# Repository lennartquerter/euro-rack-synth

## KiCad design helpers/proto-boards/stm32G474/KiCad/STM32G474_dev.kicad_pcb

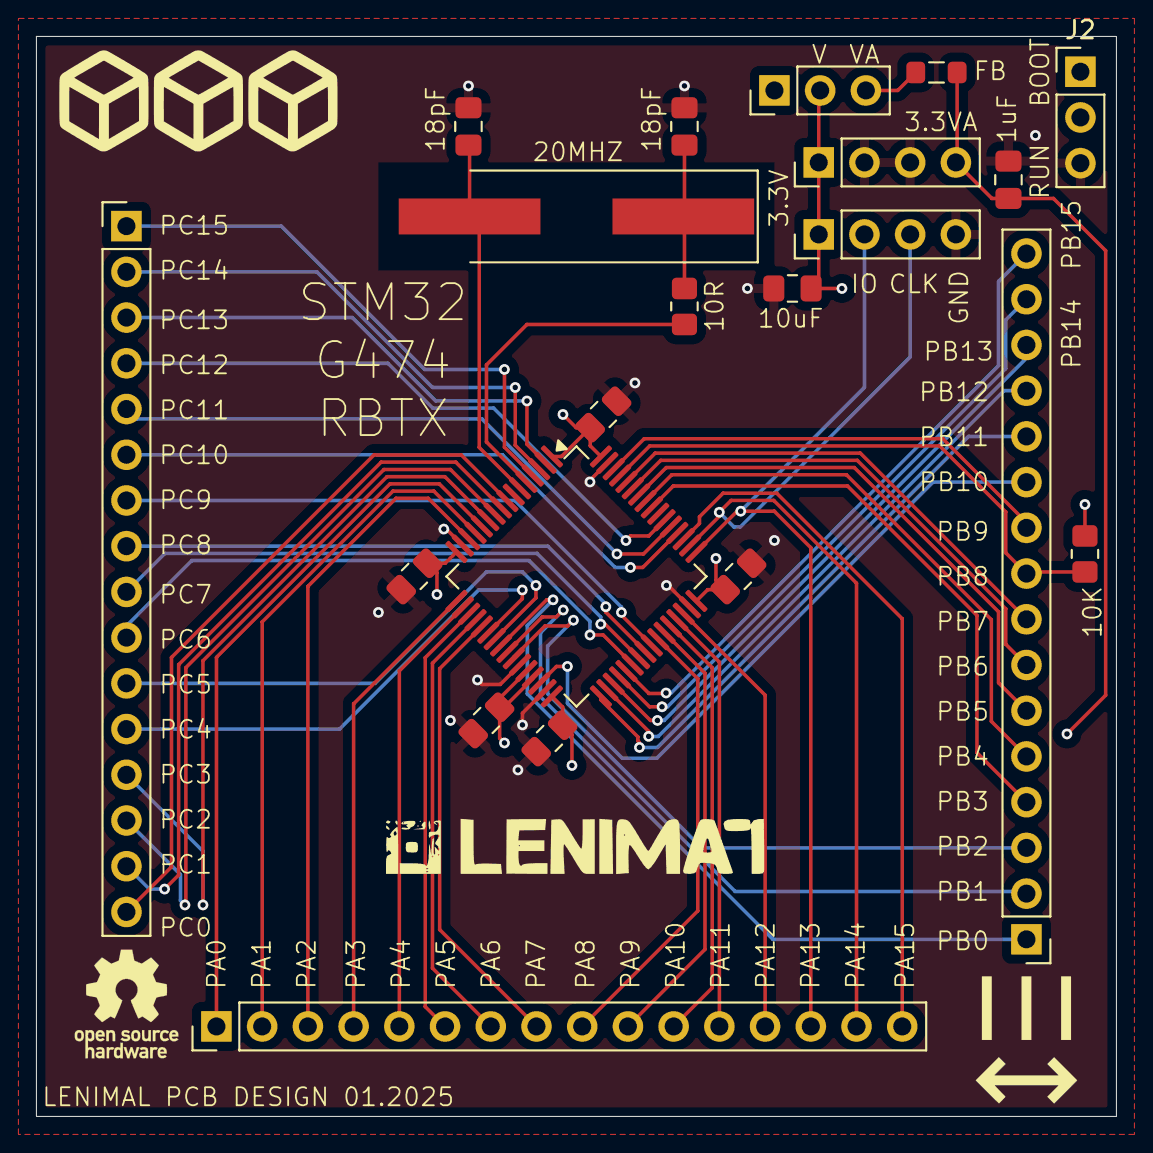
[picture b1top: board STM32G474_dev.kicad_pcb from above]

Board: 4 copper layers, 60.0 x 60.0 mm, 21 parts (0 on the bottom side), 56 nets.

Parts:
C1, C2, C3, C4, C6: 100nF; C_0805_2012Metric_Pad1.18x1.45mm_HandSolder
C5: 10uF; C_0805_2012Metric_Pad1.18x1.45mm_HandSolder
C7: 1uF; C_0805_2012Metric_Pad1.18x1.45mm_HandSolder
C9, C11: 10pF; C_0805_2012Metric_Pad1.18x1.45mm_HandSolder
FB: 120R; L_0805_2012Metric_Pad1.05x1.20mm_HandSolder
J1: SWD; PinHeader_1x04_P2.54mm_Vertical
J2: BOOT_RUN; PinHeader_1x03_P2.54mm_Vertical
J3, J4, J5: Conn_01x16; PinHeader_1x16_P2.54mm_Vertical
J6: POWER_HEADER; PinHeader_1x04_P2.54mm_Vertical
J7: V_VA_CONN; PinHeader_1x03_P2.54mm_Vertical
R2: 10R; R_0805_2012Metric_Pad1.20x1.40mm_HandSolder
R3: 10K; R_0805_2012Metric_Pad1.20x1.40mm_HandSolder
U1: STM32G474RBTx; LQFP-64_10x10mm_P0.5mm
Y1: 20MHZ; Crystal_SMD_HC49-SD_HandSoldering

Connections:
+3.3V: C1.2, C2.2, C3.2, C4.2, C5.2, J1.1, J2.1, J6.1, J7.2, U1.1 (VBAT), U1.16 (VDD), U1.32 (VDD), U1.48 (VDD), U1.64 (VDD)
+3.3VA: C6.2, C7.2, FB.1, J6.4, U1.28 (VREF+), U1.29 (VDDA)
/BOOT0: J5.9, R3.2, U1.61 (PB8)
/HSC_IN: R2.2, U1.5 (PF0)
/HSC_OUT: C11.1, U1.6 (PF1), Y1.2
/SWD_CLK: J1.3, J4.15, U1.50 (PA14)
/SWD_IO: J1.2, J4.14, U1.49 (PA13)
GNDREF: C1.1, C2.1, C3.1, C4.1, C5.1, C6.1, C7.1, C9.2, C11.2, J1.4, J2.3, J6.2, J6.3, U1.15 (VSS), U1.27 (VSSA), U1.31 (VSS), U1.47 (VSS), U1.63 (VSS)
unnamed: C9.1, R2.1, Y1.1
unnamed: J2.2, R3.1
unnamed: J3.1, U1.4 (PC15)
unnamed: J3.2, U1.3 (PC14)
unnamed: J3.3, U1.2 (PC13)
unnamed: J3.4, U1.54 (PC12)
unnamed: J3.5, U1.53 (PC11)
unnamed: J3.6, U1.52 (PC10)
unnamed: J3.7, U1.41 (PC9)
unnamed: J3.8, U1.40 (PC8)
unnamed: J3.9, U1.39 (PC7)
unnamed: J3.10, U1.38 (PC6)
unnamed: J3.11, U1.23 (PC5)
unnamed: J3.12, U1.22 (PC4)
unnamed: J3.13, U1.11 (PC3)
unnamed: J3.14, U1.10 (PC2)
unnamed: J3.15, U1.9 (PC1)
unnamed: J3.16, U1.8 (PC0)
unnamed: J4.1, U1.12 (PA0)
unnamed: J4.2, U1.13 (PA1)
unnamed: J4.3, U1.14 (PA2)
unnamed: J4.4, U1.17 (PA3)
unnamed: J4.5, U1.18 (PA4)
unnamed: J4.6, U1.19 (PA5)
unnamed: J4.7, U1.20 (PA6)
unnamed: J4.8, U1.21 (PA7)
unnamed: J4.9, U1.42 (PA8)
unnamed: J4.10, U1.43 (PA9)
unnamed: J4.11, U1.44 (PA10)
unnamed: J4.12, U1.45 (PA11)
unnamed: J4.13, U1.46 (PA12)
unnamed: J4.16, U1.51 (PA15)
unnamed: J5.1, U1.24 (PB0)
unnamed: J5.2, U1.25 (PB1)
unnamed: J5.3, U1.26 (PB2)
unnamed: J5.4, U1.56 (PB3)
unnamed: J5.5, U1.57 (PB4)
unnamed: J5.6, U1.58 (PB5)
unnamed: J5.7, U1.59 (PB6)
unnamed: J5.8, U1.60 (PB7)
unnamed: J5.10, U1.62 (PB9)
unnamed: J5.11, U1.30 (PB10)
unnamed: J5.12, U1.33 (PB11)
unnamed: J5.13, U1.34 (PB12)
unnamed: J5.14, U1.35 (PB13)
unnamed: J5.15, U1.36 (PB14)
unnamed: J5.16, U1.37 (PB15)
unnamed: FB.2, J7.3

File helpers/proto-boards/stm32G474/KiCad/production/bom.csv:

Designator,Footprint,Quantity,Value,LCSC Part #
"C1, C2, C3, C4, C6",0805,5,100nF,
"C11, C9",0805,2,10pF,
C5,0805,1,10uF,
C7,0805,1,1uF,
FB,0805,1,120R,
J1,PinHeader_1x04_P2.54mm_Vertical,1,SWD,
J2,PinHeader_1x03_P2.54mm_Vertical,1,BOOT_RUN,
"J3, J4, J5",PinHeader_1x16_P2.54mm_Vertical,3,Conn_01x16,
J6,PinHeader_1x04_P2.54mm_Vertical,1,POWER_HEADER,
J7,PinHeader_1x03_P2.54mm_Vertical,1,V_VA_CONN,
R2,0805,1,10R,
R3,0805,1,10K,
U1,LQFP-64_10x10mm_P0.5mm,1,STM32G474RBTx,
Y1,Crystal_SMD_HC49-SD_HandSoldering,1,20MHZ,

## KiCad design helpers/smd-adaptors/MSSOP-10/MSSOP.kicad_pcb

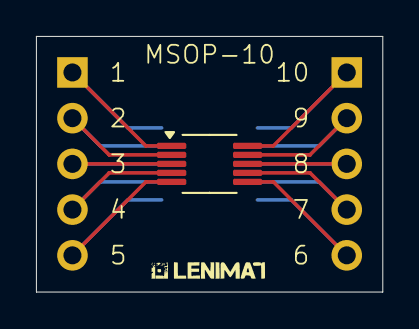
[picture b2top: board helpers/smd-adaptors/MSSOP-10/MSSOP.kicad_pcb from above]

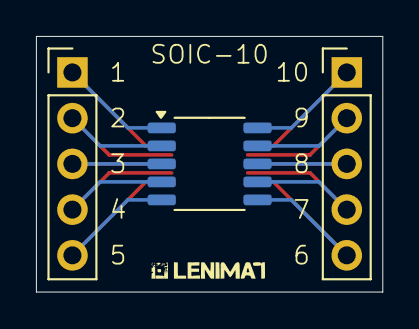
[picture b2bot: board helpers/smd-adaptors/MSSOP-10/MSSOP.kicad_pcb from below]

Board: 2 copper layers, 19.2 x 14.2 mm, 4 parts (3 on the bottom side), 10 nets.

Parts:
J1, J2: Conn_01x05; PinHeader_1x05_P2.54mm_Vertical
J3: Conn_01x10; MSOP-10_3x3mm_P0.5mm
J4: Conn_01x10; SOIC-10_3.9x4.9mm_P1mm

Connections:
unnamed: J1.1, J3.10, J4.1
unnamed: J1.2, J3.9, J4.2
unnamed: J1.3, J3.8, J4.3
unnamed: J1.4, J3.7, J4.4
unnamed: J1.5, J3.6, J4.5
unnamed: J2.1, J3.1, J4.10
unnamed: J2.2, J3.2, J4.9
unnamed: J2.3, J3.3, J4.8
unnamed: J2.4, J3.4, J4.7
unnamed: J2.5, J3.5, J4.6

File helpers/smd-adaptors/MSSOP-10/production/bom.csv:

Designator,Footprint,Quantity,Value,LCSC Part #
"J1, J2",PinHeader_1x05_P2.54mm_Vertical,2,Conn_01x05,
J3,MSOP-10_3x3mm_P0.5mm,1,Conn_01x10,
J4,SOIC-10_3.9x4.9mm_P1mm,1,Conn_01x10,

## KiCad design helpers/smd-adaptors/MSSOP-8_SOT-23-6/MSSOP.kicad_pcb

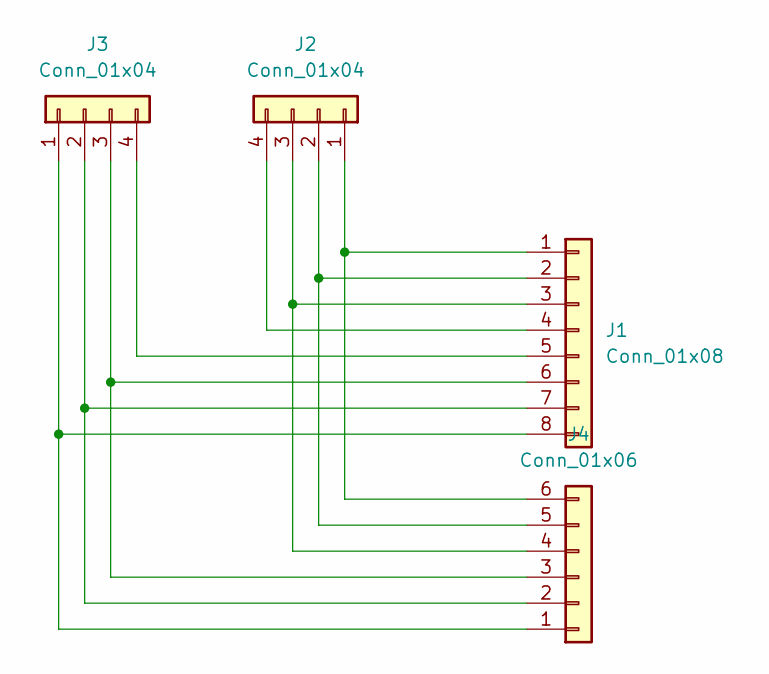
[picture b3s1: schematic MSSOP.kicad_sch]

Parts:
J1: Conn_01x08; MSOP-8_3x3mm_P0.65mm
J2, J3: Conn_01x04; PinHeader_1x04_P2.54mm_Vertical
J4: Conn_01x06; SOT-23-6_Handsoldering

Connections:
unnamed: J1.1, J2.1, J4.6
unnamed: J1.2, J2.2, J4.5
unnamed: J1.3, J2.3, J4.4
unnamed: J1.4, J2.4
unnamed: J1.5, J3.4
unnamed: J1.6, J3.3, J4.3
unnamed: J1.7, J3.2, J4.2
unnamed: J1.8, J3.1, J4.1

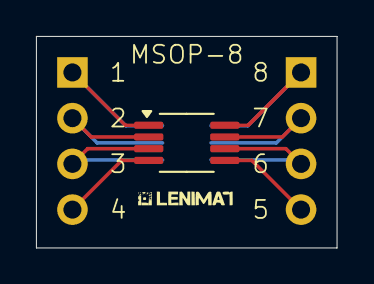
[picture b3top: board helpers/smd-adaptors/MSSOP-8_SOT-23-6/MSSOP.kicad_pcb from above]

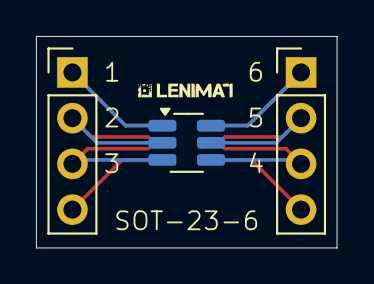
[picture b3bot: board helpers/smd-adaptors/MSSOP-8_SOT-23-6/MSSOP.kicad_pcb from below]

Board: 2 copper layers, 16.7 x 11.8 mm, 4 parts (3 on the bottom side), 8 nets.

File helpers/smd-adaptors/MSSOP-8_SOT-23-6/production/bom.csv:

Designator,Footprint,Quantity,Value,LCSC Part #
J1,MSOP-8_3x3mm_P0.65mm,1,Conn_01x08,
"J2, J3",PinHeader_1x04_P2.54mm_Vertical,2,Conn_01x04,
J4,SOT-23-6_Handsoldering,1,Conn_01x06,

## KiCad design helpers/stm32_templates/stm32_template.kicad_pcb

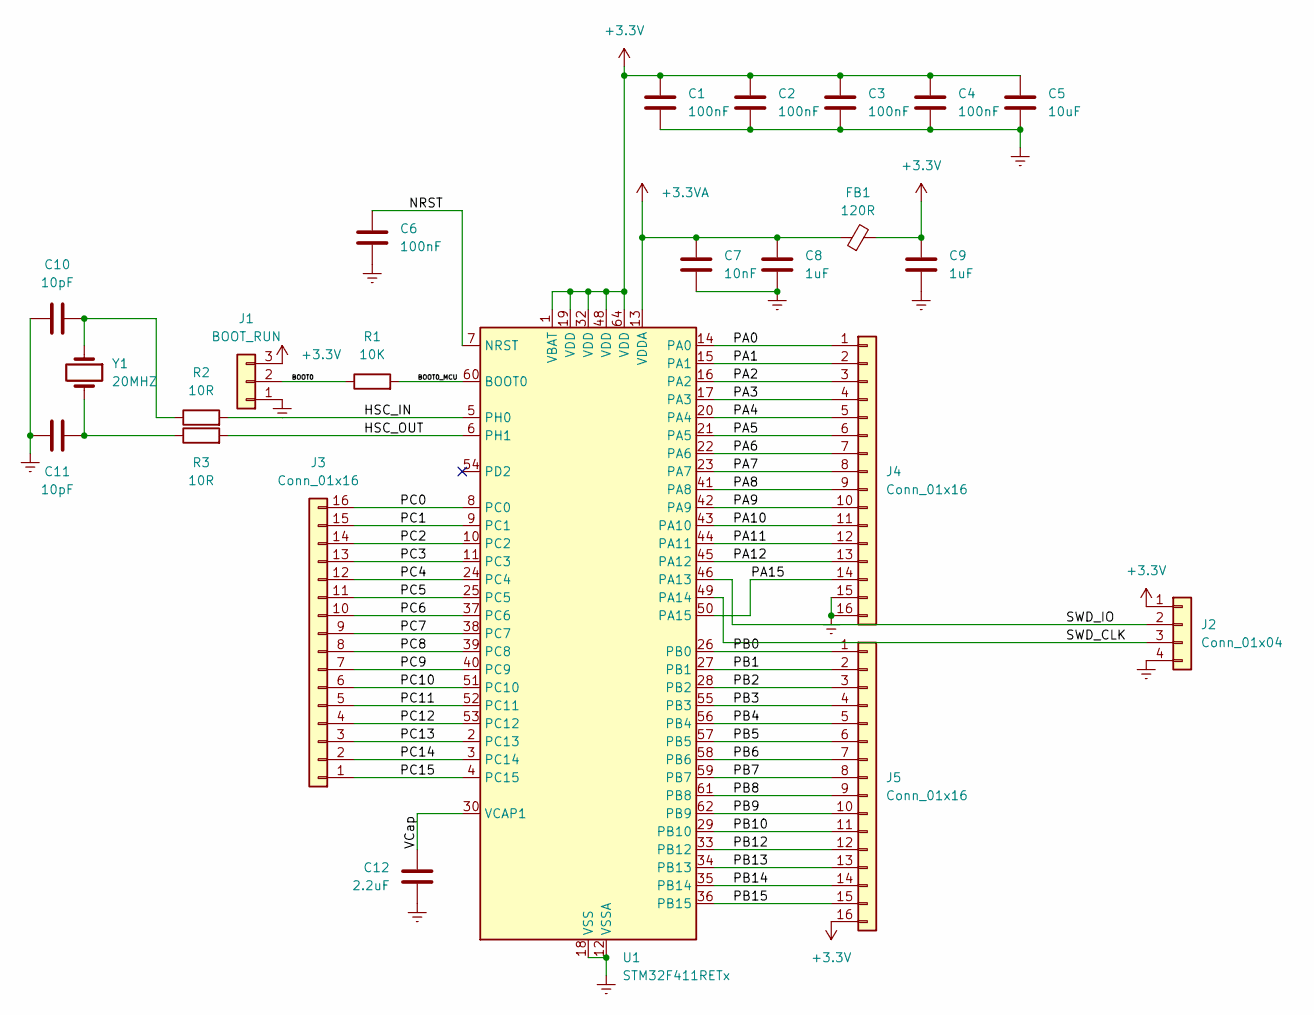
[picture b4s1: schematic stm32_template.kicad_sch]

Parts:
C1, C2, C3, C4, C6: 100nF; C_0805_2012Metric_Pad1.18x1.45mm_HandSolder
C5: 10uF; C_0805_2012Metric_Pad1.18x1.45mm_HandSolder
C7: 10nF; C_0805_2012Metric_Pad1.18x1.45mm_HandSolder
C8, C9: 1uF; C_0805_2012Metric_Pad1.18x1.45mm_HandSolder
C10, C11: 10pF; C_0805_2012Metric_Pad1.18x1.45mm_HandSolder
C12: 2.2uF; C_0805_2012Metric_Pad1.18x1.45mm_HandSolder
FB1: 120R; L_0805_2012Metric_Pad1.05x1.20mm_HandSolder
J1: BOOT_RUN; PinHeader_1x03_P2.54mm_Vertical
J2: Conn_01x04; PinHeader_1x04_P2.54mm_Vertical
J3, J4, J5: Conn_01x16; PinHeader_1x16_P2.54mm_Vertical
R1: 10K; R_0805_2012Metric_Pad1.20x1.40mm_HandSolder
R2, R3: 10R; R_0805_2012Metric_Pad1.20x1.40mm_HandSolder
U1: STM32F411RETx; LQFP-64_10x10mm_P0.5mm
Y1: 20MHZ; Crystal_SMD_HC49-SD_HandSoldering

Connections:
+3.3V: C1.2, C2.2, C3.2, C4.2, C5.2, C9.2, FB1.2, J1.3, J2.1, J5.16, U1.1 (VBAT), U1.19 (VDD), U1.32 (VDD), U1.48 (VDD), U1.64 (VDD)
+3.3VA: C7.2, C8.2, FB1.1, U1.13 (VDDA)
/BOOT0: J1.2, R1.1
/BOOT0_MCU: R1.2, U1.60 (BOOT0)
/HSC_IN: R2.2, U1.5 (PH0)
/HSC_OUT: R3.2, U1.6 (PH1)
/NRST: C6.1, U1.7 (NRST)
/PA0: J4.1, U1.14 (PA0)
/PA1: J4.2, U1.15 (PA1)
/PA2: J4.3, U1.16 (PA2)
/PA3: J4.4, U1.17 (PA3)
/PA4: J4.5, U1.20 (PA4)
/PA5: J4.6, U1.21 (PA5)
/PA6: J4.7, U1.22 (PA6)
/PA7: J4.8, U1.23 (PA7)
/PA8: J4.9, U1.41 (PA8)
/PA9: J4.10, U1.42 (PA9)
/PA10: J4.11, U1.43 (PA10)
/PA11: J4.12, U1.44 (PA11)
/PA12: J4.13, U1.45 (PA12)
/PA15: J4.14, U1.50 (PA15)
/PB0: J5.1, U1.26 (PB0)
/PB1: J5.2, U1.27 (PB1)
/PB2: J5.3, U1.28 (PB2)
/PB3: J5.4, U1.55 (PB3)
/PB4: J5.5, U1.56 (PB4)
/PB5: J5.6, U1.57 (PB5)
/PB6: J5.7, U1.58 (PB6)
/PB7: J5.8, U1.59 (PB7)
/PB8: J5.9, U1.61 (PB8)
/PB9: J5.10, U1.62 (PB9)
/PB10: J5.11, U1.29 (PB10)
/PB12: J5.12, U1.33 (PB12)
/PB13: J5.13, U1.34 (PB13)
/PB14: J5.14, U1.35 (PB14)
/PB15: J5.15, U1.36 (PB15)
/PC0: J3.16, U1.8 (PC0)
/PC1: J3.15, U1.9 (PC1)
/PC2: J3.14, U1.10 (PC2)
/PC3: J3.13, U1.11 (PC3)
/PC4: J3.12, U1.24 (PC4)
/PC5: J3.11, U1.25 (PC5)
/PC6: J3.10, U1.37 (PC6)
/PC7: J3.9, U1.38 (PC7)
/PC8: J3.8, U1.39 (PC8)
/PC9: J3.7, U1.40 (PC9)
/PC10: J3.6, U1.51 (PC10)
/PC11: J3.5, U1.52 (PC11)
/PC12: J3.4, U1.53 (PC12)
/PC13: J3.3, U1.2 (PC13)
/PC14: J3.2, U1.3 (PC14)
/PC15: J3.1, U1.4 (PC15)
/SWD_CLK: J2.3, U1.49 (PA14)
/SWD_IO: J2.2, U1.46 (PA13)
/VCap: C12.1, U1.30 (VCAP1)
GNDREF: C1.1, C2.1, C3.1, C4.1, C5.1, C6.2, C7.1, C8.1, C9.1, C10.2, C11.2, C12.2, J1.1, J2.4, J4.15, J4.16, U1.12 (VSSA), U1.18 (VSS), U1.31 (VSS), U1.47 (VSS), U1.63 (VSS)
unnamed: C10.1, R2.1, Y1.1
unnamed: C11.1, R3.1, Y1.2

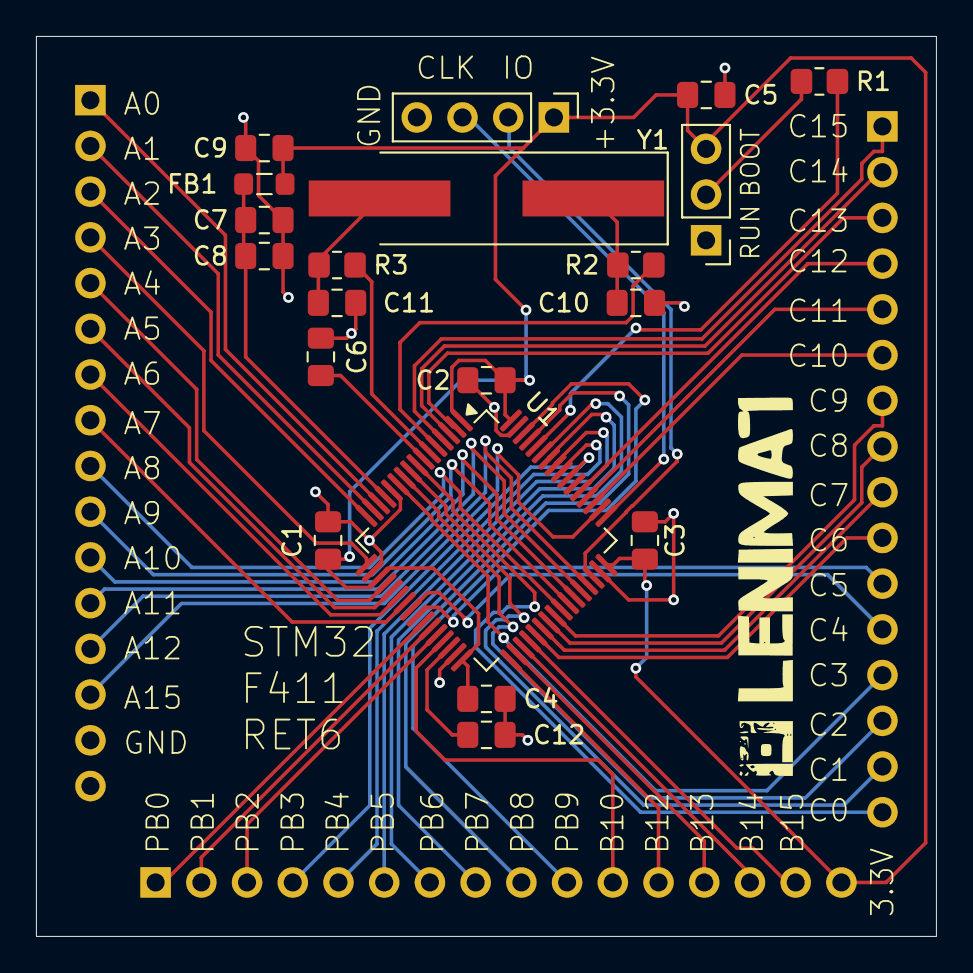
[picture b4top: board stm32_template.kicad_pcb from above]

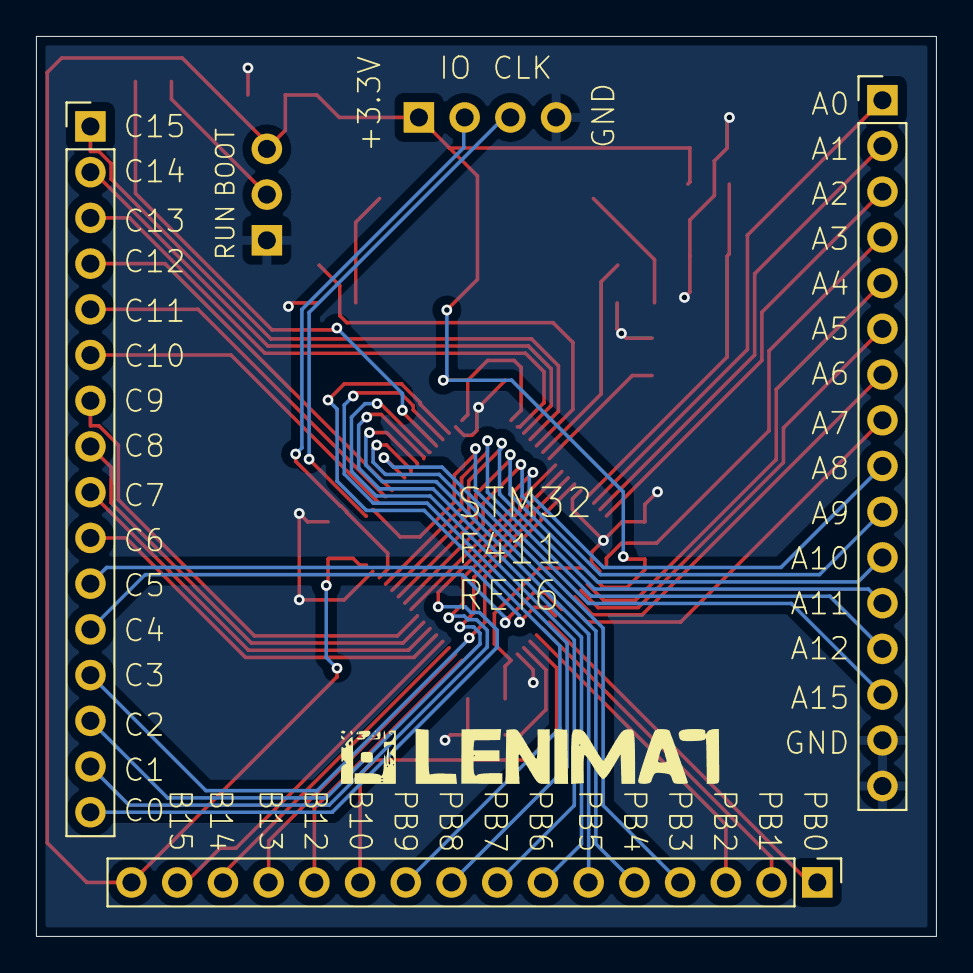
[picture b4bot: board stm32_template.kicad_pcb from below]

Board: 2 copper layers, 50.0 x 50.0 mm, 23 parts (3 on the bottom side), 58 nets.

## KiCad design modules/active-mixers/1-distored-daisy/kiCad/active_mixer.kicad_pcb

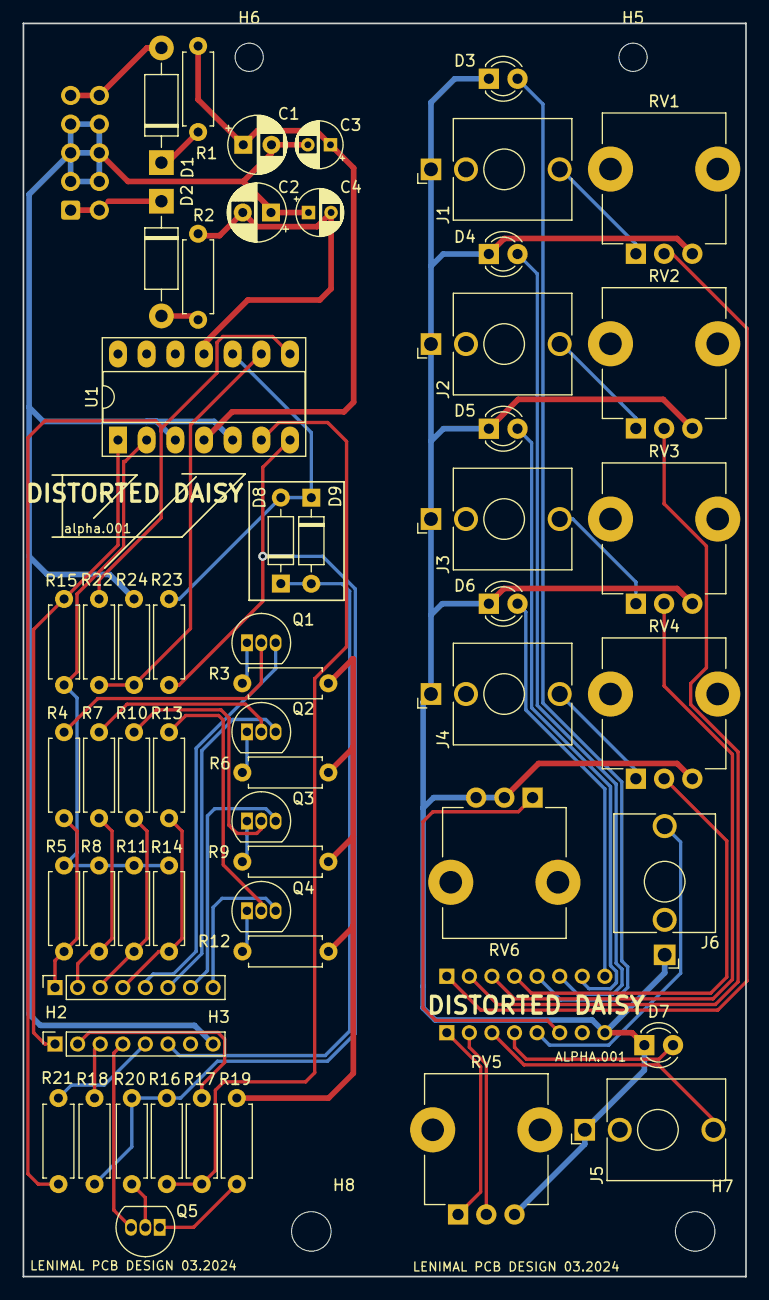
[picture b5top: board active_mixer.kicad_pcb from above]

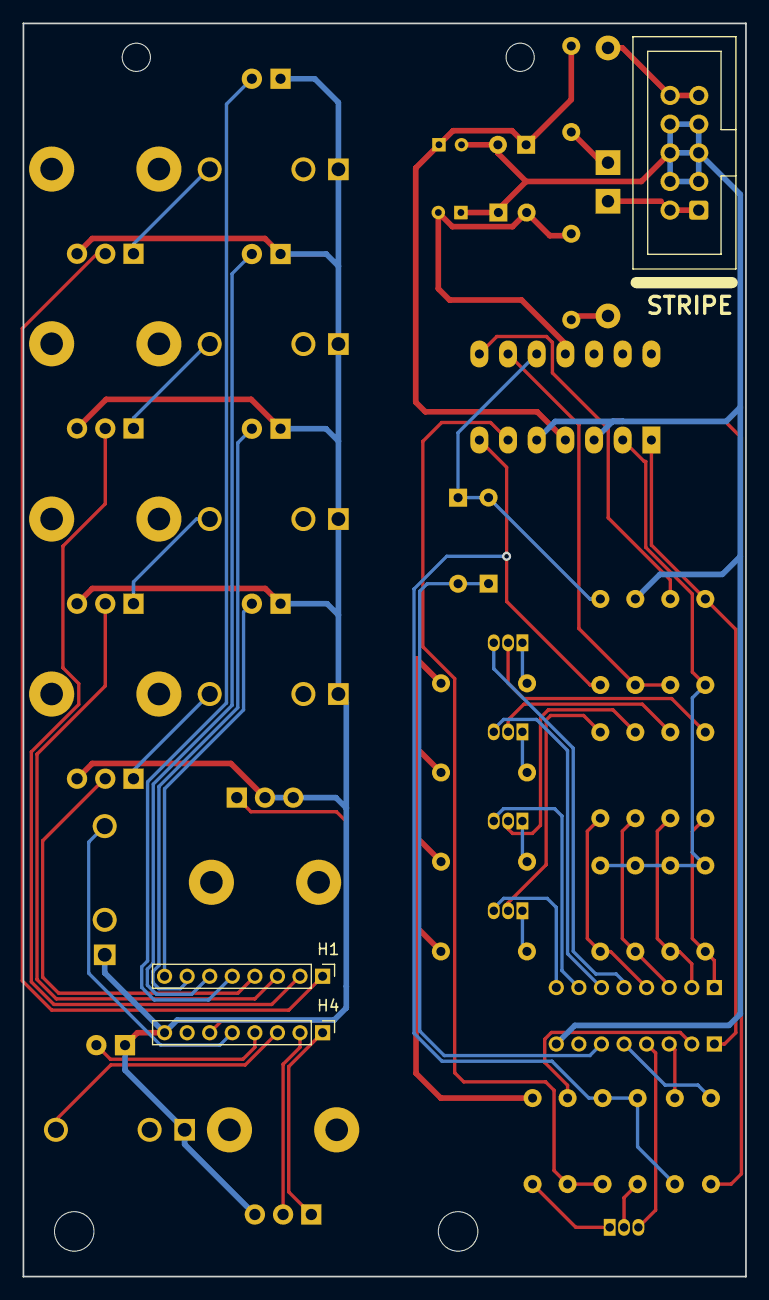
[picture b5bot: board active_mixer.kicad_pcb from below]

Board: 2 copper layers, 64.0 x 111.0 mm, 64 parts (3 on the bottom side), 55 nets.

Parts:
C1, C2: 47uF; CP_Radial_D5.0mm_P2.50mm
C3, C4: 0.1uF; CP_Radial_D4.0mm_P2.00mm
D1, D2: 1N5819; D_DO-41_SOD81_P10.16mm_Horizontal
D3: LED_IN_1; LED_D3.0mm
D4: LED_IN_2; LED_D3.0mm
D5: LED_IN_3; LED_D3.0mm
D6: LED_IN_4; LED_D3.0mm
D7: LED_OUT; LED_D3.0mm
D8, D9: 1N4148; D_DO-35_SOD27_P7.62mm_Horizontal
H1, H4: PinHeader_1x08_P2.00mm_Vertical
H2, H3: PinSocket_1x08_P2.00mm_Vertical
H5, H6: MountingHole; MountingHole_2.5mm
H7, H8: MountingHole; MountingHole_3.5mm
H9: Conn_02x05_PWR_Eurorack; CONN_02x05_PWR
J1: INPUT_1; Jack_3.5mm_QingPu_WQP-PJ398SM_Vertical_CircularHoles
J2: INPUT_2; Jack_3.5mm_QingPu_WQP-PJ398SM_Vertical_CircularHoles
J3: INPUT_3; Jack_3.5mm_QingPu_WQP-PJ398SM_Vertical_CircularHoles
J4: INPUT_4; Jack_3.5mm_QingPu_WQP-PJ398SM_Vertical_CircularHoles
J5, J6: OUTPUT; Jack_3.5mm_QingPu_WQP-PJ398SM_Vertical_CircularHoles
Q1, Q2, Q3, Q4, Q5: BC547; TO-92_Inline
R1, R2: 10; R_Axial_DIN0207_L6.3mm_D2.5mm_P7.62mm_Horizontal
R3, R6, R9, R12, R18, R19, R21: 1K; R_Axial_DIN0207_L6.3mm_D2.5mm_P7.62mm_Horizontal
R4, R5, R7, R8, R10, R11, R13, R14, R15, R16, R17, R20, R22, R24: 100K; R_Axial_DIN0207_L6.3mm_D2.5mm_P7.62mm_Horizontal
R23: 27K; R_Axial_DIN0207_L6.3mm_D2.5mm_P7.62mm_Horizontal
RV1, RV2, RV3, RV4, RV5: B100K; Potentiometer_TT_P0915N
RV6: B20K; Potentiometer_TT_P0915N
U1: TL074; DIP-14_W7.62mm_Socket_LongPads

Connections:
+12V: C1.1, C3.1, R1.2, R3.1, R6.1, R9.1, R12.1, R19.1, U1.4 (V+)
-12V: C2.2, C4.2, R2.2, U1.11 (V-)
GNDREF: C1.2, C2.1, C3.2, C4.1, D3.1 (K), D4.1 (K), D5.1 (K), D6.1 (K), D7.1 (K), H3.8, H4.8, H9.3, H9.4, H9.5, H9.6, H9.7, H9.8, J1.S, J2.S, J3.S, J4.S, J5.S, J6.S, R23.1, RV1.3, RV2.3, RV3.3, RV4.3, RV5.3, RV6.2, RV6.3, U1.3 (+), U1.5 (+)
unnamed: D1.2 (A), H9.9, H9.10
unnamed: D1.1 (K), R1.1
unnamed: D2.2 (A), R2.1
unnamed: D2.1 (K), H9.1, H9.2
unnamed: D3.2 (A), H1.5
unnamed: D4.2 (A), H1.6
unnamed: D5.2 (A), H1.7
unnamed: D6.2 (A), H1.8
unnamed: D7.2 (A), H4.4
unnamed: D8.2 (A), D9.1 (K), R24.2, U1.10 (+)
unnamed: D8.1 (K), D9.2 (A), H3.6
unnamed: H1.1, RV1.2
unnamed: H1.2, RV2.2
unnamed: H1.3, RV3.2
unnamed: H1.4, RV4.2
unnamed: H2.1, R4.1, R5.1
unnamed: H2.2, R7.1, R8.1
unnamed: H2.3, R10.1, R11.1
unnamed: H2.4, R13.1, R14.1
unnamed: H3.1, R15.2, U1.1
unnamed: H3.2, R17.1
unnamed: H3.3, R18.2
unnamed: H3.5, R21.2
unnamed: H4.1, RV5.1
unnamed: H4.2, RV5.2
unnamed: H4.3, J5.T
unnamed: H4.5, J6.T
unnamed: H4.6, RV6.1
unnamed: J1.T, RV1.1
unnamed: J2.T, RV2.1
unnamed: J3.T, RV3.1
unnamed: J4.T, RV4.1
unnamed: Q1.2 (B), R4.2
unnamed: Q1.1 (C), R3.2
unnamed: H2.5, Q1.3 (E)
unnamed: Q2.2 (B), R7.2
unnamed: Q2.1 (C), R6.2
unnamed: H2.6, Q2.3 (E)
unnamed: Q3.2 (B), R10.2
unnamed: Q3.1 (C), R9.2
unnamed: H2.7, Q3.3 (E)
unnamed: Q4.2 (B), R13.2
unnamed: Q4.1 (C), R12.2
unnamed: H2.8, Q4.3 (E)
unnamed: Q5.2 (B), R20.2
unnamed: Q5.1 (C), R19.2
unnamed: H3.4, Q5.3 (E)
unnamed: R16.2, R18.1, R20.1, R24.1, U1.7
unnamed: R21.1, R22.2, U1.8
unnamed: R5.2, R8.2, R11.2, R14.2, R15.1, U1.2 (-)
unnamed: R16.1, R17.2, U1.6 (-)
unnamed: R22.1, R23.2, U1.9 (-)

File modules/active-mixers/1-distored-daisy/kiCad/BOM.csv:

"Reference","Value","Datasheet","Footprint","Qty","DNP"
"C1,C2","47uF","~","Capacitor_THT:CP_Radial_D5.0mm_P2.50mm","2",""
"C3,C4","0.1uF","~","Capacitor_THT:CP_Radial_D4.0mm_P2.00mm","2",""
"D1,D2","1N5819","http://www.vishay.com/docs/88525/1n5817.pdf","Synth:D_DO-41_SOD81_P10.16mm_Horizontal","2",""
"D3","LED_IN_1","~","Synth:LED_D5.0mm (center Aligned)","1",""
"D4","LED_IN_2","~","Synth:LED_D5.0mm (center Aligned)","1",""
"D5","LED_IN_3","~","Synth:LED_D5.0mm (center Aligned)","1",""
"D6","LED_IN_4","~","Synth:LED_D5.0mm (center Aligned)","1",""
"D7","LED_OUT","~","Synth:LED_D5.0mm (center Aligned)","1",""
"D8,D9","1N4148","https://assets.nexperia.com/documents/data-sheet/1N4148_1N4448.pdf","Synth:D_DO-35_SOD27_P7.62mm_Horizontal","2",""
"H1,H2,H3,H4","~","~","-- mixed values --","4",""
"H5,H6,H7,H8,H10,H11,H12,H13","MountingHole","-- mixed values --","MountingHole:MountingHole_3.2mm_M3","8",""
"H9","Conn_02x05_PWR_Eurorack","~","Synth:IDC-Header_2x05_P2.54mm_Vertical","1",""
"J1","INPUT_1","~","Synth:Jack_3.5mm_QingPu_WQP-PJ398SM_Vertical_CircularHoles","1",""
"J2","INPUT_2","~","Synth:Jack_3.5mm_QingPu_WQP-PJ398SM_Vertical_CircularHoles","1",""
"J3","INPUT_3","~","Synth:Jack_3.5mm_QingPu_WQP-PJ398SM_Vertical_CircularHoles","1",""
"J4","INPUT_4","~","Synth:Jack_3.5mm_QingPu_WQP-PJ398SM_Vertical_CircularHoles","1",""
"J5","OUTPUT","~","Synth:Jack_3.5mm_QingPu_WQP-PJ398SM_Vertical_CircularHoles","1",""
"J6","INV_OUT","~","Synth:Jack_3.5mm_QingPu_WQP-PJ398SM_Vertical_CircularHoles","1",""
"Q1,Q2,Q3,Q4,Q5","BC547","https://www.onsemi.com/pub/Collateral/BC550-D.pdf","Package_TO_SOT_THT:TO-92_HandSolder","5",""
"R1,R2","10","~","Synth:R_Default (DIN0207)","2",""
"R3,R6,R9,R12,R18,R19,R21","1K","~","Synth:R_Default (DIN0207)","7",""
"R4,R5,R7,R8,R10,R11,R13,R14,R15,R16,R17,R20,R22,R24","100K","~","Synth:R_Default (DIN0207)","14",""
"R23","27K","~","Synth:R_Default (DIN0207)","1",""
"RV1,RV2,RV3,RV4,RV5","B100K","~","Synth:Potentiometer_TT_P0915N","5",""
"RV6","B20K","~","Potentiometer_THT:Potentiometer_Bourns_3296W_Vertical","1",""
"TP1","+12V","~","Connector_Pin:Pin_D1.0mm_L10.0mm","1",""
"TP2","GND","~","Connector_Pin:Pin_D1.0mm_L10.0mm","1",""
"TP3","-12V","~","Connector_Pin:Pin_D1.0mm_L10.0mm","1",""
"TP4","OUT","~","Connector_Pin:Pin_D1.0mm_L10.0mm","1",""
"TP5","DIST_OUT","~","Connector_Pin:Pin_D1.0mm_L10.0mm","1",""
"TP6","MXR_IN","~","Connector_Pin:Pin_D1.0mm_L10.0mm","1",""
"TP7","IN_1","~","Connector_Pin:Pin_D1.0mm_L10.0mm","1",""
"TP8","IN_2","~","Connector_Pin:Pin_D1.0mm_L10.0mm","1",""
"TP9","IN_3","~","Connector_Pin:Pin_D1.0mm_L10.0mm","1",""
"TP10","IN_4","~","Connector_Pin:Pin_D1.0mm_L10.0mm","1",""
"TP11","MXR_OUT","~","Connector_Pin:Pin_D1.0mm_L10.0mm","1",""
"U1","TL074","http://www.ti.com/lit/ds/symlink/tl071.pdf","Package_DIP:DIP-14_W7.62mm_Socket_LongPads","1",""

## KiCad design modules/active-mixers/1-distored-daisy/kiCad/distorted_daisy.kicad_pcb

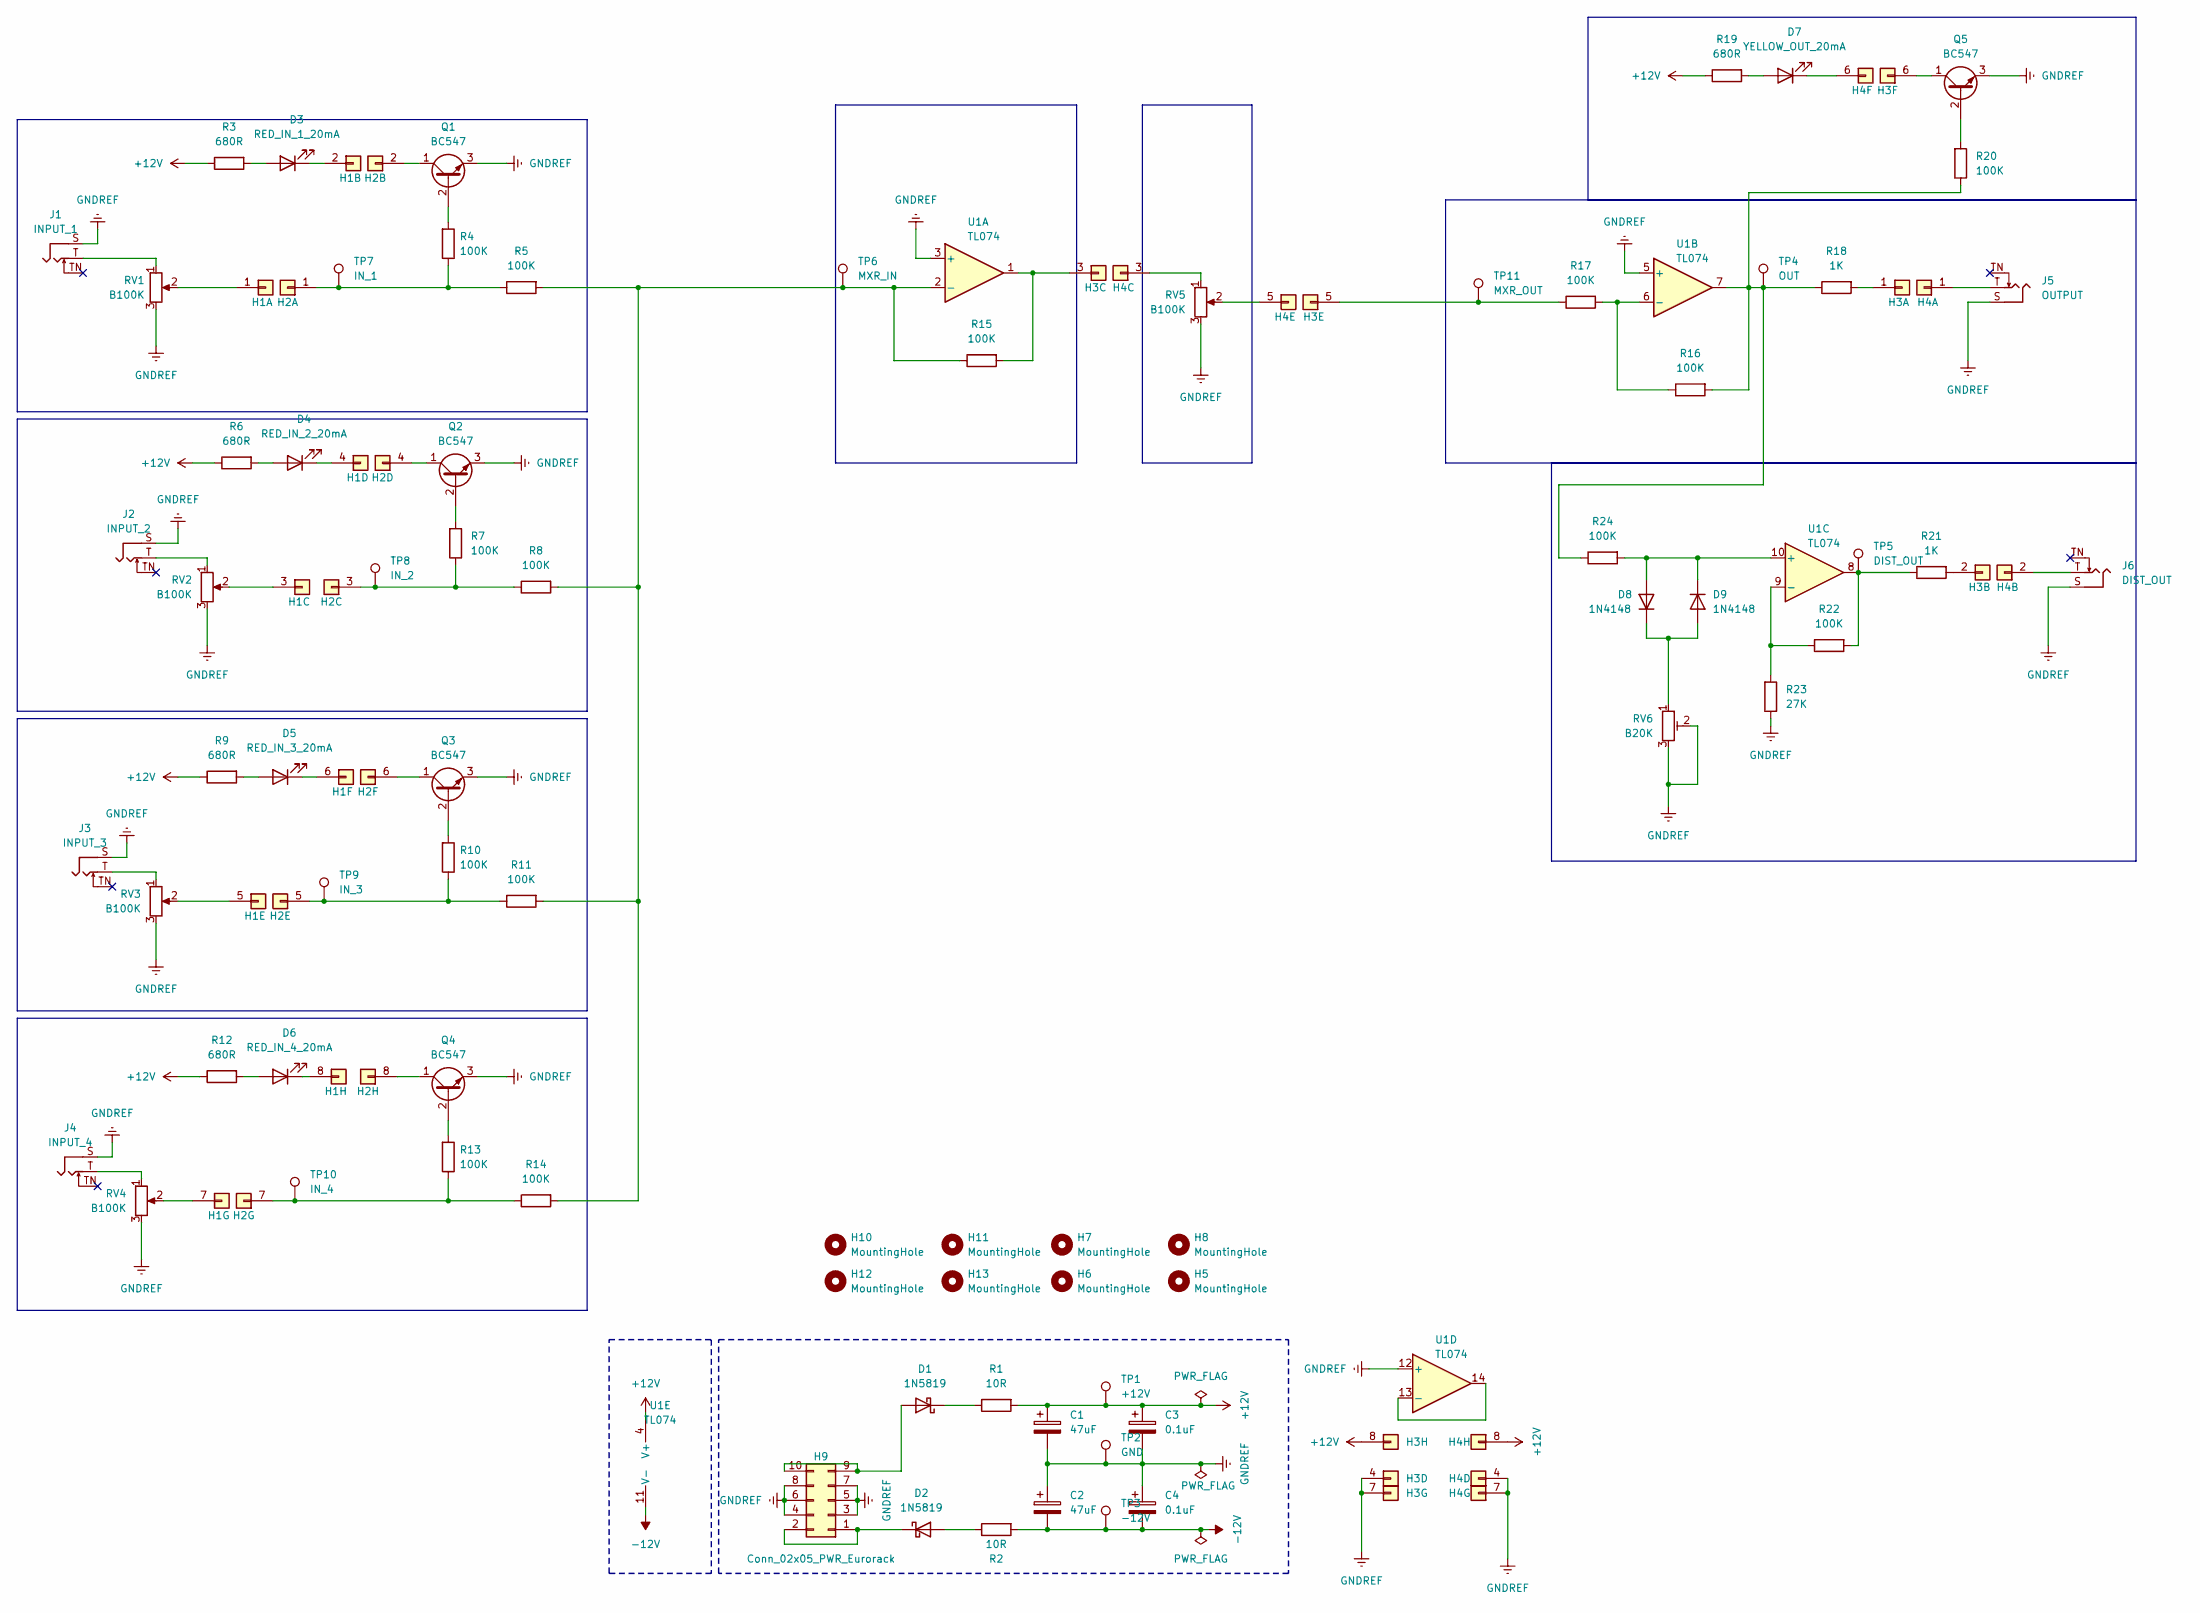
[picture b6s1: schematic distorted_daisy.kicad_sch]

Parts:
C1, C2: 47uF; CP_Radial_D5.0mm_P2.50mm
C3, C4: 0.1uF; CP_Radial_D4.0mm_P2.00mm
D1, D2: 1N5819; D_DO-41_SOD81_P10.16mm_Horizontal
D3: RED_IN_1_20mA; LED_D5.0mm (center Aligned)
D4: RED_IN_2_20mA; LED_D5.0mm (center Aligned)
D5: RED_IN_3_20mA; LED_D5.0mm (center Aligned)
D6: RED_IN_4_20mA; LED_D5.0mm (center Aligned)
D7: YELLOW_OUT_20mA; LED_D5.0mm (center Aligned)
D8, D9: 1N4148; D_DO-35_SOD27_P7.62mm_Horizontal
H1, H4: PinHeader_1x08_P2.54mm_Vertical
H2, H3: PinSocket_1x08_P2.54mm_Vertical
H5, H6, H7, H8, H10, H11, H12, H13: MountingHole; MountingHole_3.2mm_M3
H9: Conn_02x05_PWR_Eurorack; IDC-Header_2x05_P2.54mm_Vertical
J1: INPUT_1; Jack_3.5mm_QingPu_WQP-PJ398SM_Vertical_CircularHoles
J2: INPUT_2; Jack_3.5mm_QingPu_WQP-PJ398SM_Vertical_CircularHoles
J3: INPUT_3; Jack_3.5mm_QingPu_WQP-PJ398SM_Vertical_CircularHoles
J4: INPUT_4; Jack_3.5mm_QingPu_WQP-PJ398SM_Vertical_CircularHoles
J5: OUTPUT; Jack_3.5mm_QingPu_WQP-PJ398SM_Vertical_CircularHoles
J6: DIST_OUT; Jack_3.5mm_QingPu_WQP-PJ398SM_Vertical_CircularHoles
Q1, Q2, Q3, Q4, Q5: BC547; TO-92_HandSolder
R1, R2: 10R; R_Default (DIN0207)
R3, R6, R9, R12, R19: 680R; R_Default (DIN0207)
R4, R5, R7, R8, R10, R11, R13, R14, R15, R16, R17, R20, R22, R24: 100K; R_Default (DIN0207)
R18, R21: 1K; R_Default (DIN0207)
R23: 27K; R_Default (DIN0207)
RV1, RV2, RV3, RV4, RV5: B100K; Potentiometer_TT_P0915N
RV6: B20K; Potentiometer_Bourns_3296W_Vertical
TP1: +12V; Pin_D1.0mm_L10.0mm
TP2: GND; Pin_D1.0mm_L10.0mm
TP3: -12V; Pin_D1.0mm_L10.0mm
TP4: OUT; Pin_D1.0mm_L10.0mm
TP5: DIST_OUT; Pin_D1.0mm_L10.0mm
TP6: MXR_IN; Pin_D1.0mm_L10.0mm
TP7: IN_1; Pin_D1.0mm_L10.0mm
TP8: IN_2; Pin_D1.0mm_L10.0mm
TP9: IN_3; Pin_D1.0mm_L10.0mm
TP10: IN_4; Pin_D1.0mm_L10.0mm
TP11: MXR_OUT; Pin_D1.0mm_L10.0mm
U1: TL074; DIP-14_W7.62mm_Socket_LongPads

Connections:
+12V: C1.1, C3.1, H3.8, H4.8, R1.1, R3.2, R6.2, R9.2, R12.2, R19.2, TP1.1, U1.4 (V+)
-12V: C2.2, C4.2, R2.1, TP3.1, U1.11 (V-)
GNDREF: C1.2, C2.1, C3.2, C4.1, H3.4, H3.7, H4.4, H4.7, H9.3, H9.4, H9.5, H9.6, H9.7, H9.8, J1.S, J2.S, J3.S, J4.S, J5.S, J6.S, Q1.3 (E), Q2.3 (E), Q3.3 (E), Q4.3 (E), Q5.3 (E), R23.2, RV1.3, RV2.3, RV3.3, RV4.3, RV5.3, RV6.2, RV6.3, TP2.1, U1.3 (+), U1.5 (+), U1.12 (+)
unnamed: D1.2 (A), H9.9, H9.10
unnamed: D1.1 (K), R1.2
unnamed: D2.2 (A), R2.2
unnamed: D2.1 (K), H9.1, H9.2
unnamed: D3.2 (A), R3.1
unnamed: D3.1 (K), H1.2
unnamed: D4.2 (A), R6.1
unnamed: D4.1 (K), H1.4
unnamed: D5.2 (A), R9.1
unnamed: D5.1 (K), H1.6
unnamed: D6.2 (A), R12.1
unnamed: D6.1 (K), H1.8
unnamed: D7.2 (A), R19.1
unnamed: D7.1 (K), H4.6
unnamed: D8.2 (A), D9.1 (K), R24.1, U1.10 (+)
unnamed: D8.1 (K), D9.2 (A), RV6.1
unnamed: H1.1, RV1.2
unnamed: H1.3, RV2.2
unnamed: H1.5, RV3.2
unnamed: H1.7, RV4.2
unnamed: H2.1 (Pin_3), R4.2, R5.2, TP7.1
unnamed: H2.2, Q1.1 (C)
unnamed: H2.3, R7.2, R8.2, TP8.1
unnamed: H2.4, Q2.1 (C)
unnamed: H2.5, R10.2, R11.2, TP9.1
unnamed: H2.6, Q3.1 (C)
unnamed: H2.7, R13.2, R14.2, TP10.1
unnamed: H2.8, Q4.1 (C)
unnamed: H3.1, R18.1
unnamed: H3.2, R21.1
unnamed: H3.3, R15.1, U1.1
unnamed: H3.5, R17.2, TP11.1
unnamed: H3.6, Q5.1 (C)
unnamed: H4.1 (Pin_3), J5.T
unnamed: H4.2, J6.T
unnamed: H4.3, RV5.1
unnamed: H4.5, RV5.2
unnamed: J1.T, RV1.1
unnamed: J2.T, RV2.1
unnamed: J3.T, RV3.1
unnamed: J4.T, RV4.1
unnamed: Q1.2 (B), R4.1
unnamed: Q2.2 (B), R7.1
unnamed: Q3.2 (B), R10.1
unnamed: Q4.2 (B), R13.1
unnamed: Q5.2 (B), R20.1
unnamed: R16.1, R18.2, R20.2, R24.2, TP4.1, U1.7
unnamed: R21.2, R22.1, TP5.1, U1.8
unnamed: R5.1, R8.1, R11.1, R14.1, R15.2, TP6.1, U1.2 (-)
unnamed: R16.2, R17.1, U1.6 (-)
unnamed: R22.2, R23.1, U1.9 (-)
unnamed: U1.13 (-), U1.14
